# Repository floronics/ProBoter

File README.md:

# PROBoter - A platform for automated embedded system security analysis

## Floronics-Nachbau

Dieser Fork von [SCHUTZWERK/PROBoter](https://github.com/schutzwerk/PROBoter)
sammelt unsere Unterlagen für einen nachvollziehbaren Nachbau. Die
[Bestellliste](bom/Bestellliste.md) ist ein **Arbeitsstand ohne Bestellfreigabe**:
Das CAD-Modell enthält Platzhalter; elektrische Zuordnungen und
Fertigungsangaben sind noch offen. Offene Positionen sind ausdrücklich markiert.

| Unterlage | Inhalt |
|---|---|
| [Nachbau-Übersicht](docs/Floronics-Nachbau.md) | Struktur, Herkunft und nächster Schritt |
| [Quellen](docs/Quellen.md) | Öffentlich zugängliche Belege und Lizenzhinweise |
| [Aufbau](docs/Aufbau.md) | Mechanik, Elektronik und Software im Überblick |
| [Bestellliste](bom/Bestellliste.md) | Menschenlesbare Beschaffungsplanung |
| [CAD-Teileliste](bom/CAD-Teileliste.md) | Alle 120 benannten Blattteile mit Mengen und Klärstatus |
| [Offene Punkte](docs/Offene-Punkte.md) | Entscheidungen vor Konstruktion und Bestellung |

---

The PROBoter is a hardware and software platform to automate embedded system security analysis. The initial prototype was developed during the master's thesis **Automatisierung der hardwarenahen Sicherheitsanalyse von eingebetteten Systemen** in cooperation with [SCHUTZWERK GmbH](https://www.schutzwerk.com) and
[Hochschule Kempten](https://www.hs-kempten.de) in the context of the [SecForCARs](https://www.secforcars.de) project.

The project consists of various components which can be found in individual subfolders of this repository:

- [firmware](/firmware) Contains the firmware running on the 3D printer boards driving the PROBoter hardware platform.
- [hardware](/hardware) Contains 3D models and construction data of the PROBoter hardware platform.
- [image_data_sets](/image_data_sets) Contains image data sets to train or validate algorithms for IC and pin detection.
- [publications](/publications) Contains publications related to the PROBoter. You can also find citation information here if you want to reference our work in other research publications.
- [software](/software) Contains software components forming the high-level software part of the PROBoter platform.

Most parts of the platform are licensed under the [GNU General Public License v3.0](https://www.gnu.org/licenses/gpl-3.0.txt). Detailed license information and used third-party components can be found in the individual subfolders.

Other components will be released soon. Follow the [SCHUTZWERK PROBoter blog post series](https://schutzwerk.com/en/43/posts/proboter_01/) to get updates of the current development status and new component releases. So stay tuned... :)

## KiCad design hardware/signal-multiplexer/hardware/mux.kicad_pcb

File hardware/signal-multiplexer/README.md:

# PROBoter signal multiplexer board

Aktuell schaltet das Board (`mux.kicad_sch`) jeden Eingangskanal (I1–I4, B1–B4) per Relais
(K1–K7, je über NMOS Q1–Q8 vom ATmega328PB angesteuert) wahlweise auf einen von zwei
Oszilloskop-Ausgängen (SCOPE-A / SCOPE-B).

## Konzept (offen, noch nicht umgesetzt): Oszi/Multimeter-Umschaltung pro Probe

Idee: zusätzlich zur Oszi-Umschaltung soll pro (beweglicher) Probe auch zwischen
Oszilloskop und Multimeter umgeschaltet werden können, statt feste Probes pro
Instrument (eine fest fürs Oszi, eine fest für Multimeter+, eine für GND, eine für
Power) zu verwenden.

**Empfohlener Ansatz:** Hybridlösung.
- **GND und Power fest verdrahtet lassen**, nicht mitmultiplexen. Beide werden während
  einer Messung durchgehend gebraucht; ein Umschalten der GND-Referenz mitten in der
  Messung erzeugt Spannungsspitzen bzw. kurzzeitiges Floating.
- **Signal-Probe(s) per Relais zwischen Oszi und Multimeter umschaltbar**, nach
  demselben Muster wie die bestehende SCOPE-A/SCOPE-B-Umschaltung (zusätzliche
  Relais-Stufe/-Bus fürs Multimeter pro Kanal). Das passt zur vorhandenen Architektur
  und erspart getrennte Roboter-Bewegungen/Probes für denselben Testpunkt.

**Zu beachtende Trade-offs:**
- Jede zusätzliche Relais-Stufe im Oszi-Pfad erhöht parasitäre Kapazität und
  Kontaktwiderstand → Bandbreitenverlust beim Oszi. Multimeter-Messungen (meist
  DC/langsam) sind davon kaum betroffen.
- Multimeter sind im Widerstands-/Durchgangs-/Dioden-Modus **aktiv** (speisen Strom
  bzw. Spannung ein), ein Oszi-Eingang ist rein passiv hochohmig. Oszi und Multimeter
  dürfen daher nie gleichzeitig am selben Knoten hängen → Umschaltung muss
  break-before-make sein, sonst drohen Messfehler oder Kurzschlüsse zwischen den
  Instrumenten.

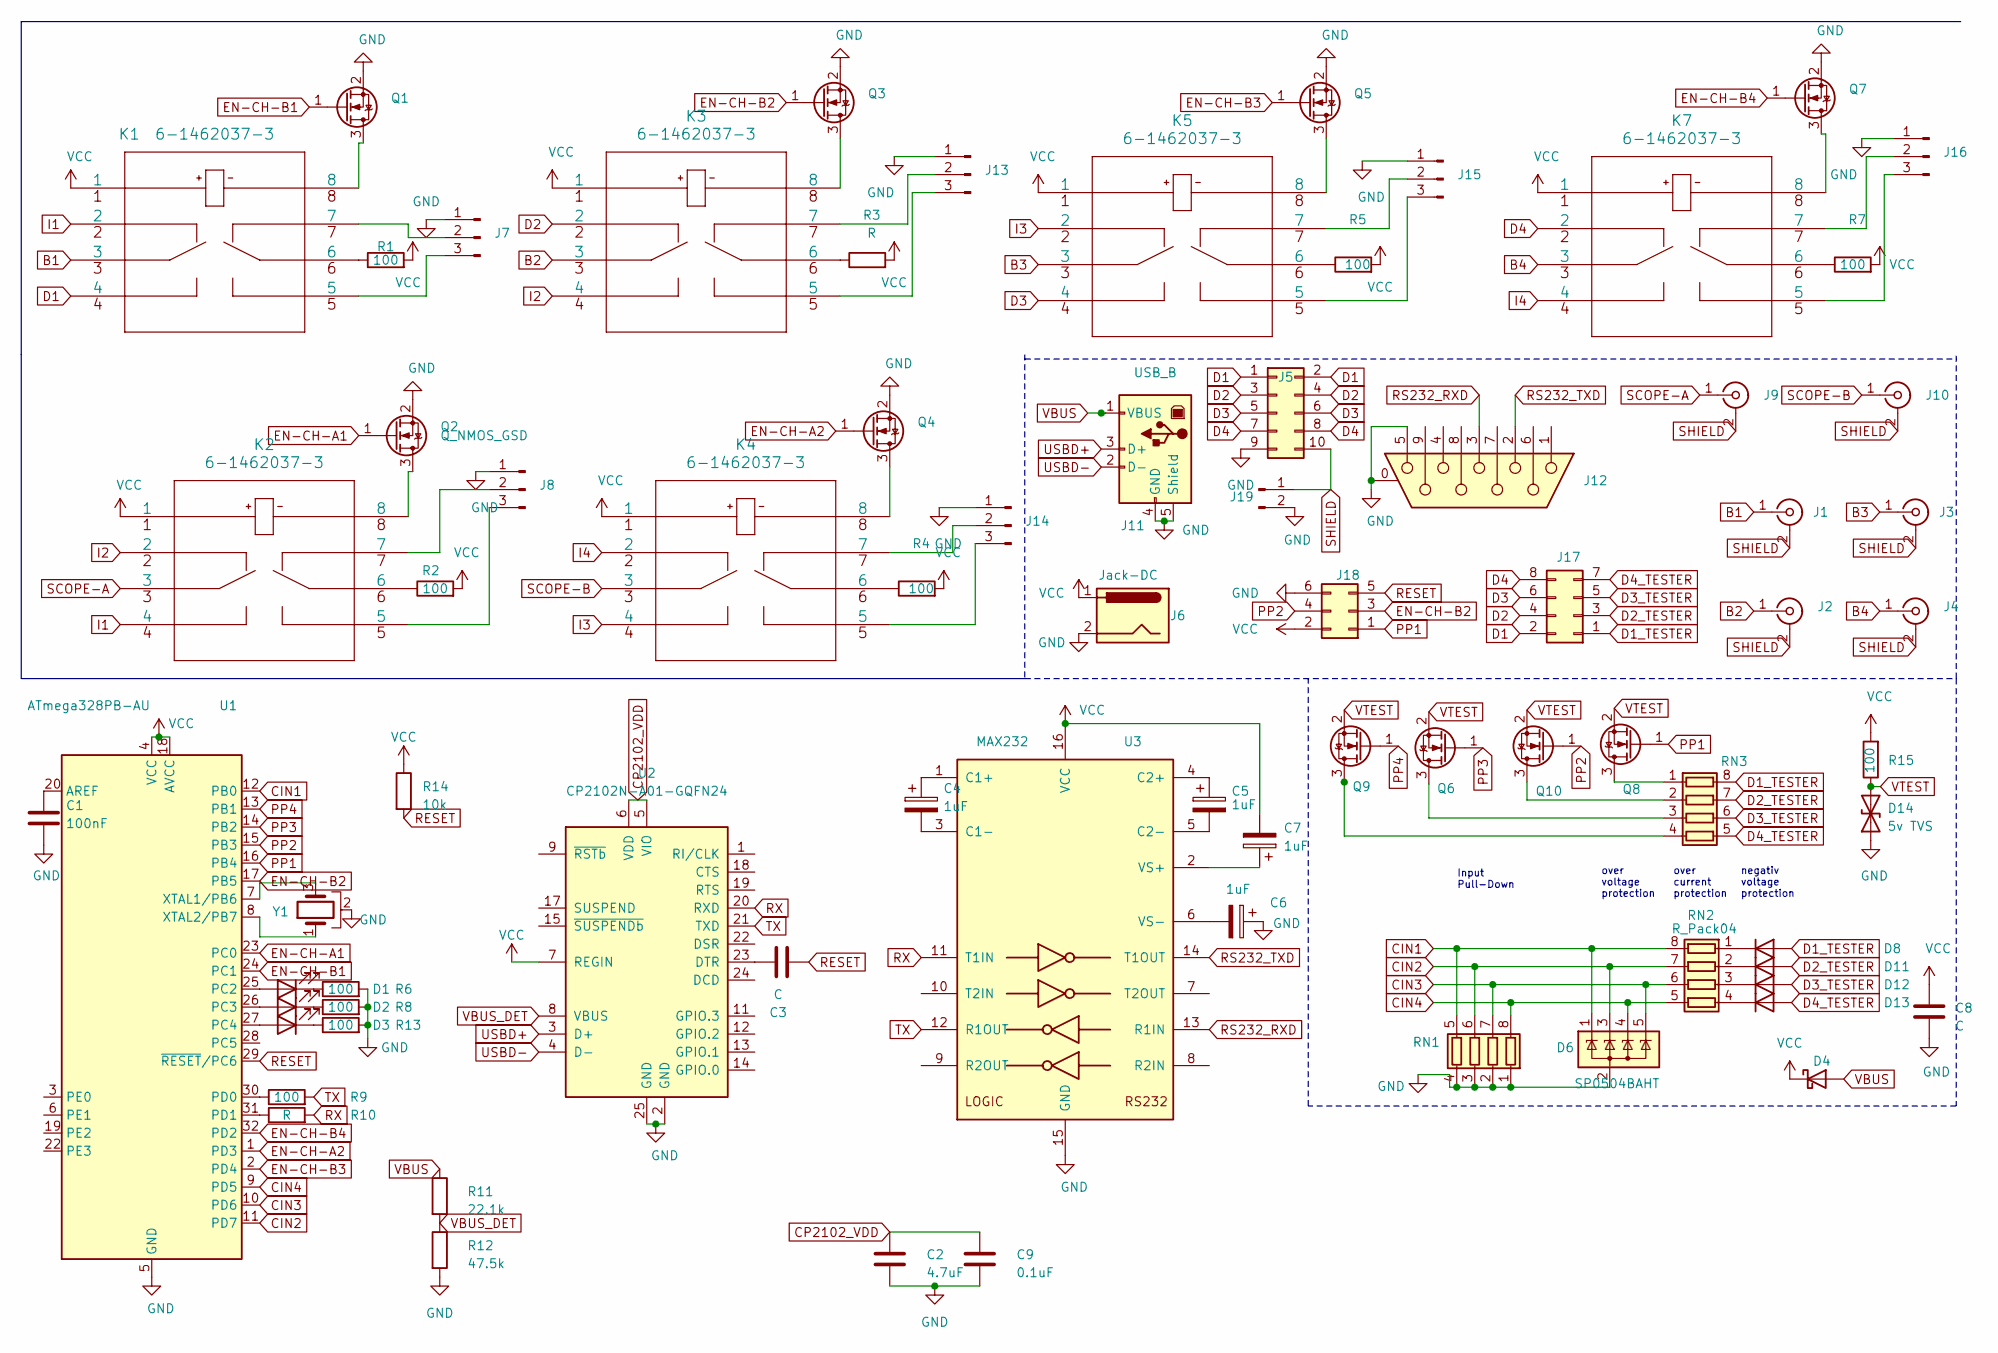
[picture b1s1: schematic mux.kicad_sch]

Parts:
C1: 100nF; CP_EIA-1608-08_AVX-J_Pad1.25x1.05mm_HandSolder
C2: 4.7uF; C_0805_2012Metric
C3: C; CP_EIA-1608-08_AVX-J_Pad1.25x1.05mm_HandSolder
C4, C5, C6, C7: 1uF; CP_EIA-1608-08_AVX-J_Pad1.25x1.05mm_HandSolder
C8: C; C_0805_2012Metric
C9: 0.1uF; C_0805_2012Metric
D1, D2, D3: LED; LED_D3.0mm_Horizontal_O3.81mm_Z6.0mm
D4: D_Schottky; D_SOD-123
D6: SP0504BAHT; SOT-23-5
D8, D11, D12, D13: D; D_0805_2012Metric
D14: 5v TVS; D_0805_2012Metric
J1, J2, J3, J4, J9, J10: Conn_Coaxial; SMA_Molex_73251-2200_Horizontal
J5: Conn_02x04_Odd_Even; PinHeader_2x05_P2.54mm_Horizontal
J6: Jack-DC; BarrelJack_Wuerth_6941xx301002
J7, J8, J13, J14, J15, J16: Conn_01x03_Male; JST_PH_B3B-PH-K_1x03_P2.00mm_Vertical
J11: USB_B; USB_B_Lumberg_2411_02_Horizontal
J12: DB9_Female_MountingHoles; DSUB-9_Female_Horizontal_P2.77x2.84mm_EdgePinOffset7.70mm_H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
J17: Conn_02x04_Odd_Even; PinHeader_2x04_P2.54mm_Vertical
J18: Conn_02x03_Odd_Even; PinHeader_2x03_P2.54mm_Vertical
J19: Conn_01x02_Male; PinHeader_1x02_P2.54mm_Vertical
K1, K2, K3, K4, K5, K7: 6-1462037-3
Q1, Q2, Q3, Q4, Q5, Q6, Q7, Q8, Q9, Q10: Q_NMOS_GSD; SOT-23
R1, R2, R4, R5, R6, R7, R8, R9, R13, R15: 100; R_0805_2012Metric
R3, R10: R; R_0805_2012Metric
R11: 22.1k; R_0805_2012Metric
R12: 47.5k; R_0805_2012Metric
R14: 10k; R_0805_2012Metric
RN1, RN2, RN3: R_Pack04; R_Array_Convex_4x0603
U1: ATmega328PB-AU; TQFP-32_7x7mm_P0.8mm
U2: CP2102N-A01-GQFN24; QFN-24-1EP_4x4mm_P0.5mm_EP2.6x2.6mm
U3: MAX232; SOIC-16_3.9x9.9mm_P1.27mm
Y1: Crystal_GND2; Resonator_SMD_Murata_CSTxExxV-3Pin_3.0x1.1mm_HandSoldering

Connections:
B1: J1.1 (In), K1.3
B2: J2.1 (In), K3.3
B3: J3.1 (In), K5.3
B4: J4.1 (In), K7.3
CIN1: D6.1 (K), RN1.5 (R4.2), RN2.8 (R1.2), U1.12 (PB0)
CIN2: D6.3 (K), RN1.6 (R3.2), RN2.7 (R2.2), U1.11 (PD7)
CIN3: D6.5 (K), RN1.7 (R2.2), RN2.6 (R3.2), U1.10 (PD6)
CIN4: D6.4 (K), RN1.8 (R1.2), RN2.5 (R4.2), U1.9 (PD5)
CP2102_VDD: C2.1, C9.1, U2.5 (VIO), U2.6 (VDD)
D1: J5.1, J5.2, J17.2, K1.4
D1_TESTER: D8.2 (A), J17.1, RN3.8 (R1.2)
D2: J5.3, J5.4, J17.4, K3.2
D2_TESTER: D11.2 (A), J17.3, RN3.7 (R2.2)
D3: J5.5, J5.6, J17.6, K5.4
D3_TESTER: D12.2 (A), J17.5, RN3.6 (R3.2)
D4: J5.7, J5.8, J17.8, K7.2
D4_TESTER: D13.2 (A), J17.7, RN3.5 (R4.2)
EN-CH-A1: Q2.1 (G), U1.23 (PC0)
EN-CH-A2: Q4.1 (G), U1.1 (PD3)
EN-CH-B1: Q1.1 (G), U1.24 (PC1)
EN-CH-B2: J18.3, Q3.1 (G), U1.17 (PB5)
EN-CH-B3: Q5.1 (G), U1.2 (PD4)
EN-CH-B4: Q7.1 (G), U1.32 (PD2)
GND: C1.2, C2.2, C6.1, C8.2, C9.2, D6.2 (A), D14.1 (A1), J5.9, J6.2, J7.1, J8.1, J11.4 (GND), J11.5 (Shield), J12.0 (PAD), J12.5, J13.1, J14.1, J15.1, J16.1, J18.6, J19.2, Q1.2 (S), Q2.2 (S), Q3.2 (S), Q4.2 (S), Q5.2 (S), Q7.2 (S), R6.2, R8.2, R12.2, R13.2, RN1.1 (R1.1), RN1.2 (R2.1), RN1.3 (R3.1), RN1.4 (R4.1), U1.5 (GND), U1.21 (GND), U2.2 (GND), U2.25 (GND), U3.15 (GND), Y1.2
I1: K1.2, K2.4
I2: K2.2, K3.4
I3: K4.4, K5.2
I4: K4.2, K7.4
unnamed: C1.1, U1.20 (AREF)
unnamed: C3.2, U2.23 (DTR)
unnamed: C4.1, U3.1 (C1+)
unnamed: C4.2, U3.3 (C1-)
unnamed: C5.1, U3.4 (C2+)
unnamed: C5.2, U3.5 (C2-)
unnamed: C6.2, U3.6 (VS-)
unnamed: C7.1, U3.2 (VS+)
unnamed: D1.1 (K), R6.1
unnamed: D1.2 (A), U1.25 (PC2)
unnamed: D2.1 (K), R8.1
unnamed: D2.2 (A), U1.26 (PC3)
unnamed: D3.1 (K), R13.1
unnamed: D3.2 (A), U1.27 (PC4)
unnamed: D8.1 (K), RN2.1 (R1.1)
unnamed: D11.1 (K), RN2.2 (R2.1)
unnamed: D12.1 (K), RN2.3 (R3.1)
unnamed: D13.1 (K), RN2.4 (R4.1)
unnamed: J7.2, K1.7
unnamed: J7.3, K1.5
unnamed: J8.2, K2.7
unnamed: J8.3, K2.5
unnamed: J13.2, K3.7
unnamed: J13.3, K3.5
unnamed: J14.2, K4.7
unnamed: J14.3, K4.5
unnamed: J15.2, K5.7
unnamed: J15.3, K5.5
unnamed: J16.2, K7.7
unnamed: J16.3, K7.5
unnamed: K1.6, R1.1
unnamed: K1.8, Q1.3 (D)
unnamed: K2.6, R2.1
unnamed: K2.8, Q2.3 (D)
unnamed: K3.6, R3.1
unnamed: K3.8, Q3.3 (D)
unnamed: K4.6, R4.1
unnamed: K4.8, Q4.3 (D)
unnamed: K5.6, R5.1
unnamed: K5.8, Q5.3 (D)
unnamed: K7.6, R7.1
unnamed: K7.8, Q7.3 (D)
unnamed: Q6.3 (D), RN3.3 (R3.1)
unnamed: Q8.3 (D), RN3.1 (R1.1)
unnamed: Q9.3 (D), RN3.4 (R4.1)
unnamed: Q10.3 (D), RN3.2 (R2.1)
unnamed: R9.1, U1.30 (PD0)
unnamed: R10.1, U1.31 (PD1)
unnamed: U1.7 (XTAL1/PB6), Y1.3
unnamed: U1.8 (XTAL2/PB7), Y1.1
PP1: J18.1, Q8.1 (G), U1.16 (PB4)
PP2: J18.4, Q10.1 (G), U1.15 (PB3)
PP3: Q6.1 (G), U1.14 (PB2)
PP4: Q9.1 (G), U1.13 (PB1)
RESET: C3.1, J18.5, R14.2, U1.29 (~RESET~/PC6)
RS232_RXD: J12.3, U3.13 (R1IN)
RS232_TXD: J12.2, U3.14 (T1OUT)
RX: R10.2, U2.20 (RXD), U3.11 (T1IN)
SCOPE-A: J9.1 (In), K2.3
SCOPE-B: J10.1 (In), K4.3
SHIELD: J1.2 (Ext), J2.2 (Ext), J3.2 (Ext), J4.2 (Ext), J5.10, J9.2 (Ext), J10.2 (Ext), J19.1
TX: R9.2, U2.21 (TXD), U3.12 (R1OUT)
USBD+: J11.3 (D+), U2.3 (D+)
USBD-: J11.2 (D-), U2.4 (D-)
VBUS: D4.2 (A), J11.1 (VBUS), R11.1
VBUS_DET: R11.2, R12.1, U2.8 (VBUS)
VCC: C7.2, C8.1, D4.1 (K), J6.1, J18.2, K1.1, K2.1, K3.1, K4.1, K5.1, K7.1, R1.2, R2.2, R3.2, R4.2, R5.2, R7.2, R14.1, R15.2, U1.4 (VCC), U1.18 (AVCC), U2.7 (REGIN), U3.16 (VCC)
VTEST: D14.2 (A2), Q6.2 (S), Q8.2 (S), Q9.2 (S), Q10.2 (S), R15.1

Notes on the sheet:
Input Pull-Down
over voltage protection
over current protection
negativ voltage protection

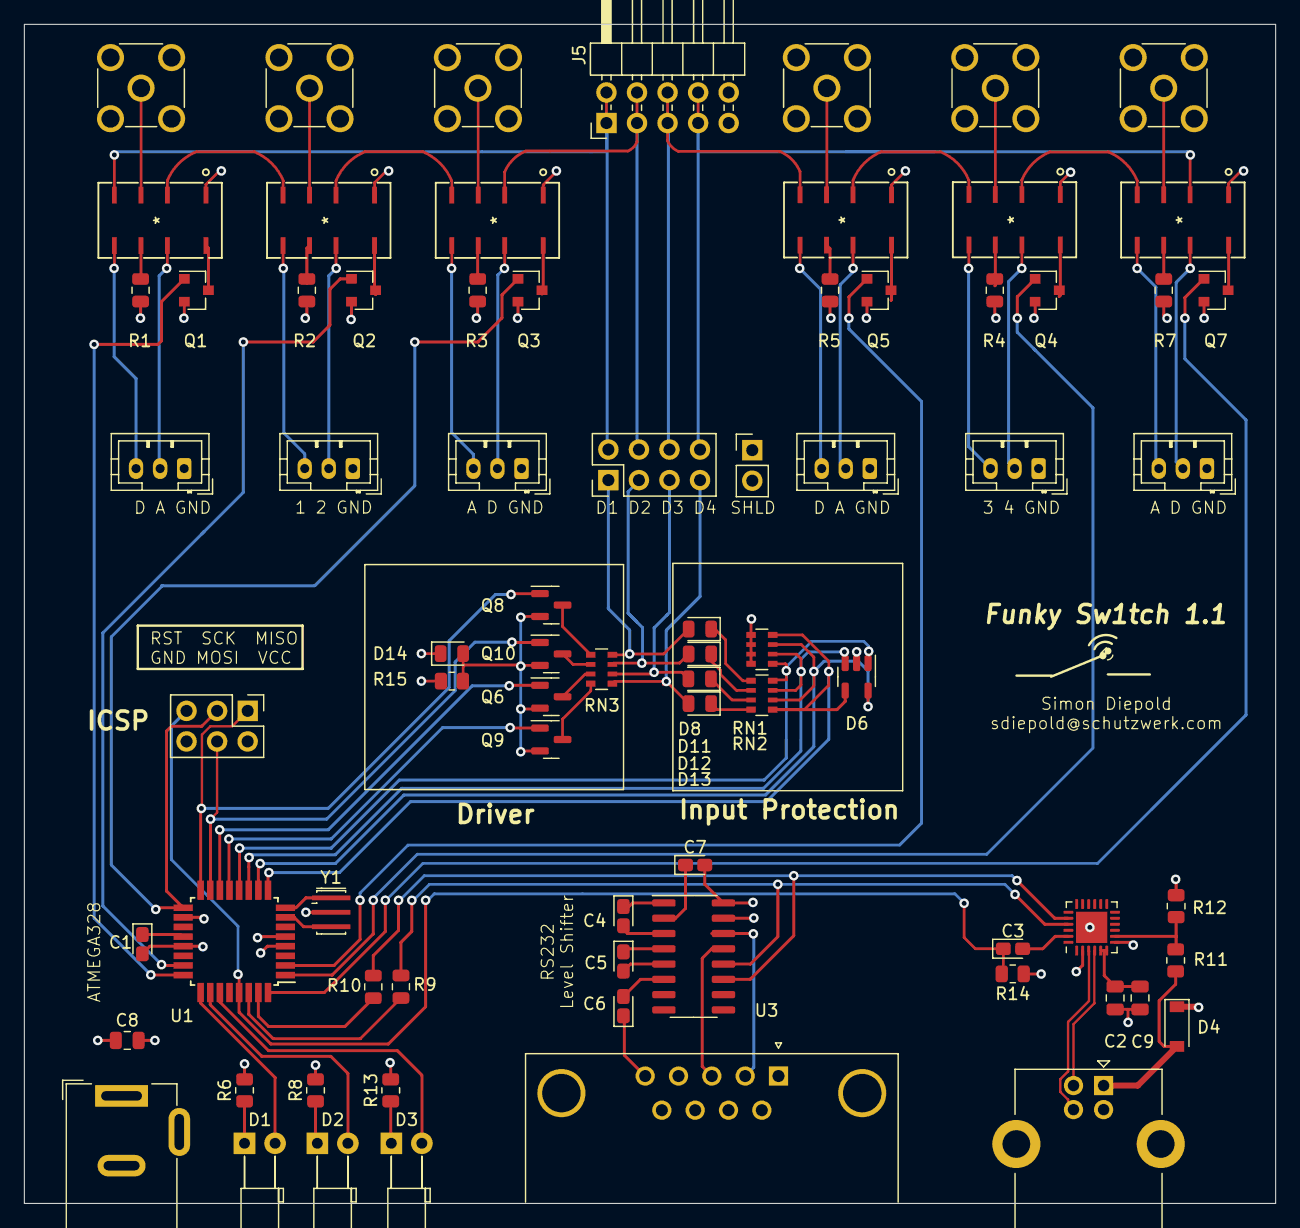
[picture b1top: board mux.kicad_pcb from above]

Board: 4 copper layers, 104.0 x 98.0 mm, 76 parts (0 on the bottom side), 96 nets.

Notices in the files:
parts and their libraries:
Copyright 2016 Accelerated Designs. All rights reserved.
